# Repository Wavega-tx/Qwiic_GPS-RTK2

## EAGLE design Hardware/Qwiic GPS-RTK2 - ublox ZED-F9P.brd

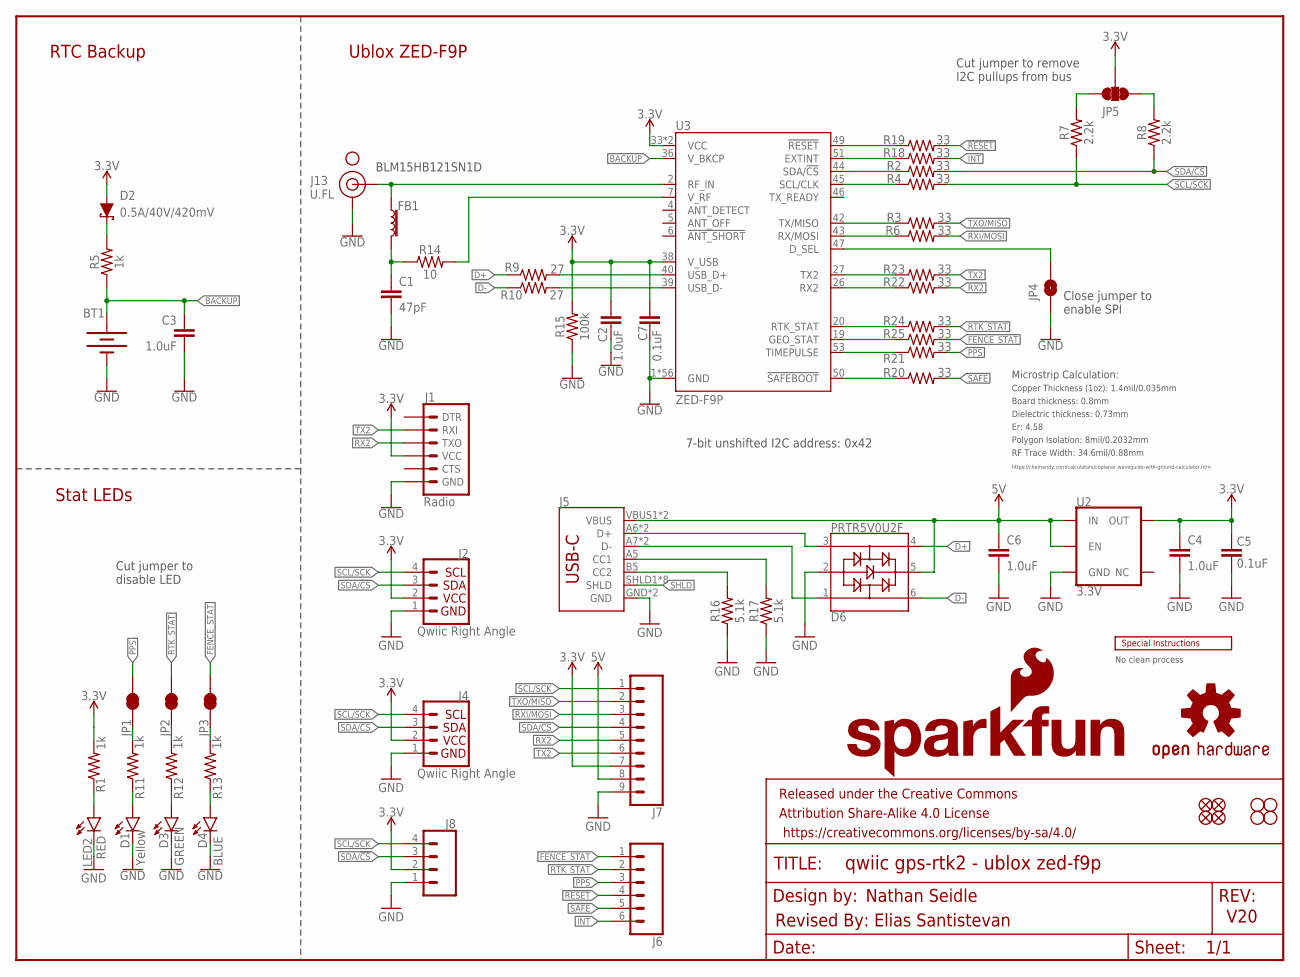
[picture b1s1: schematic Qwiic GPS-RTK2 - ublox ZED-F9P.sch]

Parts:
BT1: ML414H_IV01E_BATTERY; ML414H_IV01E
C1: 47pF; 0603
C2, C3, C4, C6: 1.0uF; 0603
C5, C7: 0.1uF; 0603
D1: Yellow; LED-0603
D2: 0.5A/40V/420mV; SOD-323
D3: GREEN; LED-0603
D4: BLUE; LED-0603
D6: PRTR5V0U2F; SOT886
FB1: FERRITE_BEAD-120_OHM-0402; 0402
FRAME1: FRAME-LETTER; CREATIVE_COMMONS
J1: Radio; 1X06_NO_SILK
J2, J4: Qwiic Right Angle; JST04_1MM_RA
J5: USB_C2-LAYER; USB-C-16P
J6: CONN_06NO_SILK_FEMALE_PTH; 1X06_NO_SILK
J7: CONN_09NO_SILK; 1X09_NO_SILK
J8: CONN_041X04_NO_SILK; 1X04_NO_SILK
J13: U.FL
JP1, JP2, JP3: JUMPER-SMT_2_NC_TRACE_SILK; SMT-JUMPER_2_NC_TRACE_SILK
JP4: JUMPER-SMT_2_NO_SILK; SMT-JUMPER_2_NO_SILK
JP5: JUMPER-SMT_3_2-NC_TRACE_SILK; SMT-JUMPER_3_2-NC_TRACE_SILK
JP21, JP61, JP71, JP81: FIDUCIALUFIDUCIAL; FIDUCIAL-MICRO
JP31, JP41, JP91, JP101: STAND-OFFTIGHT; STAND-OFF-TIGHT
LED2: RED; LED-0603
LOGO1: OSHW-LOGOMINI; OSHW-LOGO-MINI
LOGO2: SFE_LOGO_NAME_FLAME.1_INCH; SFE_LOGO_NAME_FLAME_.1
R1, R5, R11, R12, R13: 1k; 0603
R2, R3, R4, R6, R18, R19, R20, R21, R22, R23, R24, R25: 33; 0603
R7, R8: 2.2k; 0603
R9, R10: 27; 0603
R14: 10; 0603
R15: 100k; 0603
R16, R17: 5.1k; 0603
U2: 3.3V; SOT23-5
U3: ZED-F9P
U$2: SPECIAL_INSTRUCTIONS-ORDERING; ORDERING_INSTRUCTIONS
U$54: SMA-ANTENNA-THREADED; SMA-THREADED

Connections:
3.3V: C2.1, C4.1, C5.2, C7.2, D2.A, J1.4 (VCC), J2.2, J4.2, J7.7, J8.2, JP5.2, R1.2, R15.2, U2.5 (OUT), U3.33 (VCC), U3.34 (VCC), U3.38 (V_USB)
5V: C6.1, D6.5, J5.VBUS1 (VBUS), J5.VBUS2 (VBUS), J7.8, U2.1 (IN), U2.3 (EN)
!RESET: J6.4, R19.2
!SAFE: J6.5, R20.2
ANT_VCC: C1.1, FB1.2, R14.1
BACKUP: BT1.+, C3.1, R5.1, U3.36 (V_BKCP)
CC1: J5.A5 (CC1), R17.2
CC2: J5.B5 (CC2), R16.2
D+: D6.4, R9.1
D-: D6.6, R10.1
D_SEL: JP4.2, U3.47 (D_SEL)
FENCE_STAT: J6.1, JP3.2, R25.2
GND: BT1.-, C1.2, C2.2, C3.2, C4.2, C5.1, C6.2, C7.1, D1.C, D3.C, D4.C, D6.2, J1.6 (GND), J2.1, J4.1, J5.GND, J5.GND2 (GND), J7.9, J8.1, J13.1 (GND), J13.2 (GND), JP4.1, LED2.C, R15.1, R16.1, R17.1, U2.2 (GND), U3.1 (GND), U3.3 (GND), U3.12 (GND), U3.14 (GND), U3.32 (GND), U3.37 (GND), U3.41 (GND), U3.48 (GND), U3.55 (GND), U3.56 (GND), U3.57 (GND), U3.58 (GND), U3.59 (GND), U3.60 (GND), U3.61 (GND), U3.62 (GND), U3.63 (GND), U3.64 (GND), U3.65 (GND), U3.66 (GND), U3.67 (GND), U3.68 (GND), U3.69 (GND), U3.70 (GND), U3.71 (GND), U3.72 (GND), U3.73 (GND), U3.74 (GND), U3.75 (GND), U3.76 (GND), U3.77 (GND), U3.78 (GND), U3.79 (GND), U3.80 (GND), U3.81 (GND), U3.82 (GND), U3.83 (GND), U3.84 (GND), U3.85 (GND), U3.86 (GND), U3.87 (GND), U3.88 (GND), U3.89 (GND), U3.90 (GND), U3.91 (GND), U3.92 (GND), U3.93 (GND), U3.94 (GND), U3.95 (GND), U3.96 (GND), U3.97 (GND), U3.98 (GND), U3.99 (GND), U3.100 (GND), U3.101 (GND), U3.102 (GND)
GPS_ANT1: FB1.1, J13.FEED (SIGNAL), U3.2 (RF_IN)
INT: J6.6, R18.2
unnamed: D3.A, R12.1
unnamed: D1.A, R11.1
unnamed: JP2.1, R12.2
unnamed: JP1.1, R11.2
unnamed: JP5.1, R8.2
unnamed: D2.C, R5.2
unnamed: D4.A, R13.1
unnamed: JP5.3, R7.2
unnamed: JP3.1, R13.2
unnamed: LED2.A, R1.1
unnamed: R9.2, U3.40 (USB_D+)
unnamed: R10.2, U3.39 (USB_D-)
unnamed: R14.2, U3.7 (V_RF)
unnamed: R22.1, U3.26 (RX2)
unnamed: R18.1, U3.51 (EXTINT)
unnamed: R19.1, U3.49 (!RESET!)
unnamed: R21.1, U3.53 (TIMEPULSE)
unnamed: R20.1, U3.50 (!SAFEBOOT!)
unnamed: R24.1, U3.20 (RTK_STAT)
unnamed: R25.1, U3.19 (GEO_STAT)
PPS: J6.3, JP1.2, R21.2
RTK_STAT: J6.2, JP2.2, R24.2
RX2: J1.3 (TXO), J7.5, R22.2
RXI/MOSI: J7.3, R6.2
RXLV: R6.1, U3.43 (RX/MOSI)
SCL/SCK: J2.4, J4.4, J7.1, J8.4, R4.2, R7.1
SCL_LV: R4.1, U3.45 (SCL/CLK)
SDA/!CS: J2.3, J4.3, J7.4, J8.3, R2.2, R8.1
SDA_LV: R2.1, U3.44 (SDA/!CS!)
SHLD: J5.SHLD1 (SHLD), J5.SHLD2 (SHLD), J5.SHLD3 (SHLD), J5.SHLD4 (SHLD), J5.SHLD5 (SHLD), J5.SHLD6 (SHLD), J5.SHLD7 (SHLD), J5.SHLD8 (SHLD)
TX2: J1.2 (RXI), J7.6, R23.2
TX2_P: R23.1, U3.27 (TX2)
TXLV: R3.1, U3.42 (TX/MISO)
TXO/MISO: J7.2, R3.2
UNP_D+: D6.3, J5.A6 (D+), J5.B6 (D+)
UNP_D-: D6.1, J5.A7 (D-), J5.B7 (D-)

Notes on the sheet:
V20
7-bit unshifted I2C address: 0x42
Ublox ZED-F9P
RTC Backup
Stat LEDs
Cut jumper to remove I2C pullups from bus
Cut jumper to disable LED
Close jumper to enable SPI
BLM15HB121SN1D
Board thickness: 0.8mm
Er: 4.58
Copper Thickness (1oz): 1.4mil/0.035mm
RF Trace Width: 34.6mil/0.88mm
Polygon Isolation: 8mil/0.2032mm
No clean process
Dielectric thickness: 0.73mm
https://chemandy.com/calculators/coplanar-waveguide-with-ground-calculator.htm
Microstrip Calculation:
Nathan Seidle
Revised By: Elias Santistevan

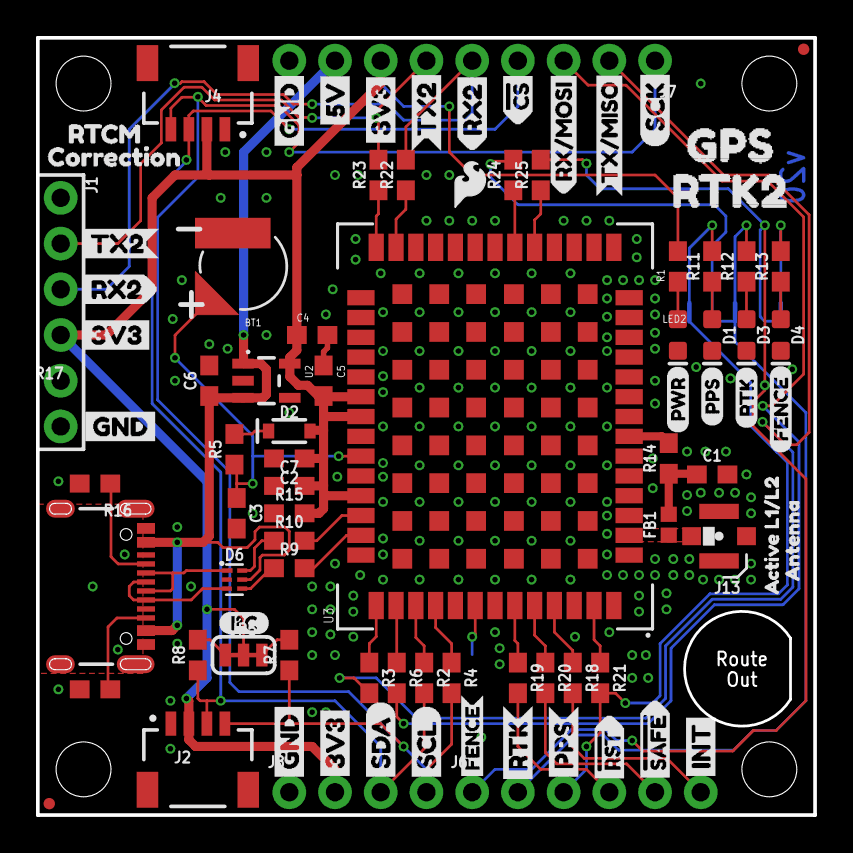
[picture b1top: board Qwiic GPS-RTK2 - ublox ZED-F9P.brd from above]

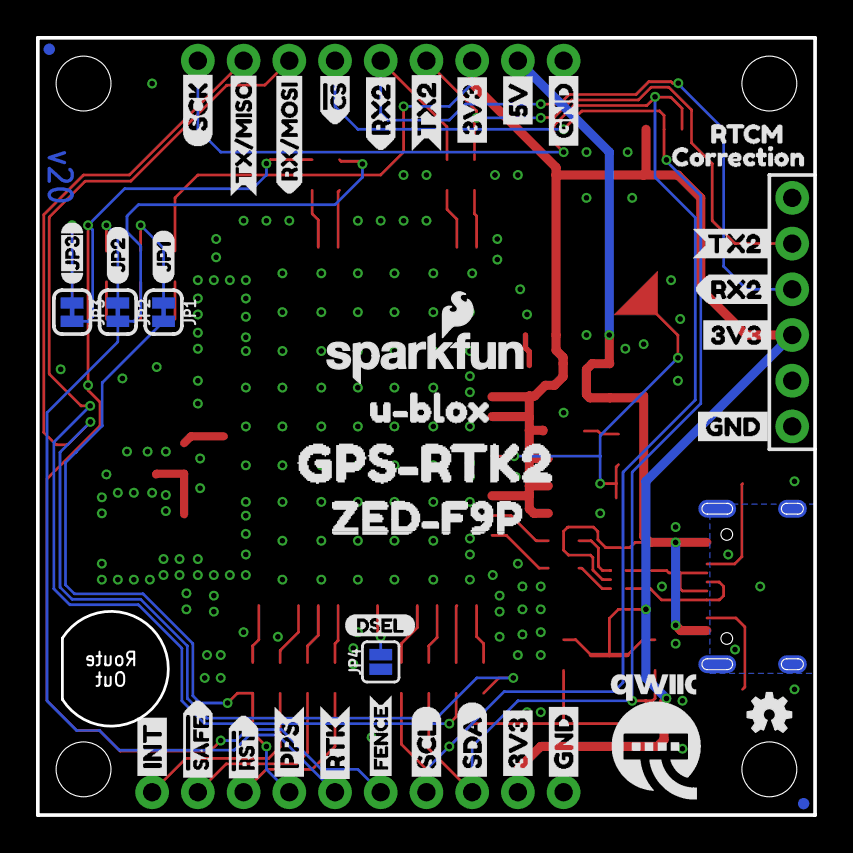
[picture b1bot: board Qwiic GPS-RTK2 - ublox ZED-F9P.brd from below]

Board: 2 copper layers, 43.2 x 43.2 mm, 136 parts (41 on the bottom side), 51 nets.

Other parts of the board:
U$1, U$4: SDA-[)
U$3, U$5: SCL-[)
U$6, U$7, U$60, U$61, U$66, U$67: 3V3-04
U$8, U$9, U$62, U$63: GND-04
U$10: I_SUPER2_C-()-03
U$11: FENCE2
U$12: JP20
U$13, U$28, U$29: RTK1
U$14, U$17: FENCE0
U$15, U$16: INT8
U$18: PWR-()-03
U$19, U$20: 5V
U$21, U$56, U$58: RX20
U$22: U#BLOX3
U$23, U$24: CS#-<]
U$25: JP10
U$26, U$31: RX#MOSI3
U$27: DSEL0
U$30: QWIIC-LOGO-MEDIUM
U$32: JP32
U$33: SFE_LOGO_FLAME_.1
U$34, U$37: TX#MISO1
U$35, U$36: #RST3
U$38, U$41: SCK-(]-04
U$39, U$40: #SAFE1
U$42: RX22
U$43, U$44: PPS5
U$45, U$68: GND3
U$46: GPS#RTK28
U$48, U$70: RTCM5
U$49: ZED#F9P6
U$50, U$55, U$57: TX21
U$51: TX23
U$52: PPS0
U$53, U$69: CORRECTION0
U$59: GPS0
U$64: RTK21
U$65: ACTIVE_L1#L21
U$71: ANTENNA2

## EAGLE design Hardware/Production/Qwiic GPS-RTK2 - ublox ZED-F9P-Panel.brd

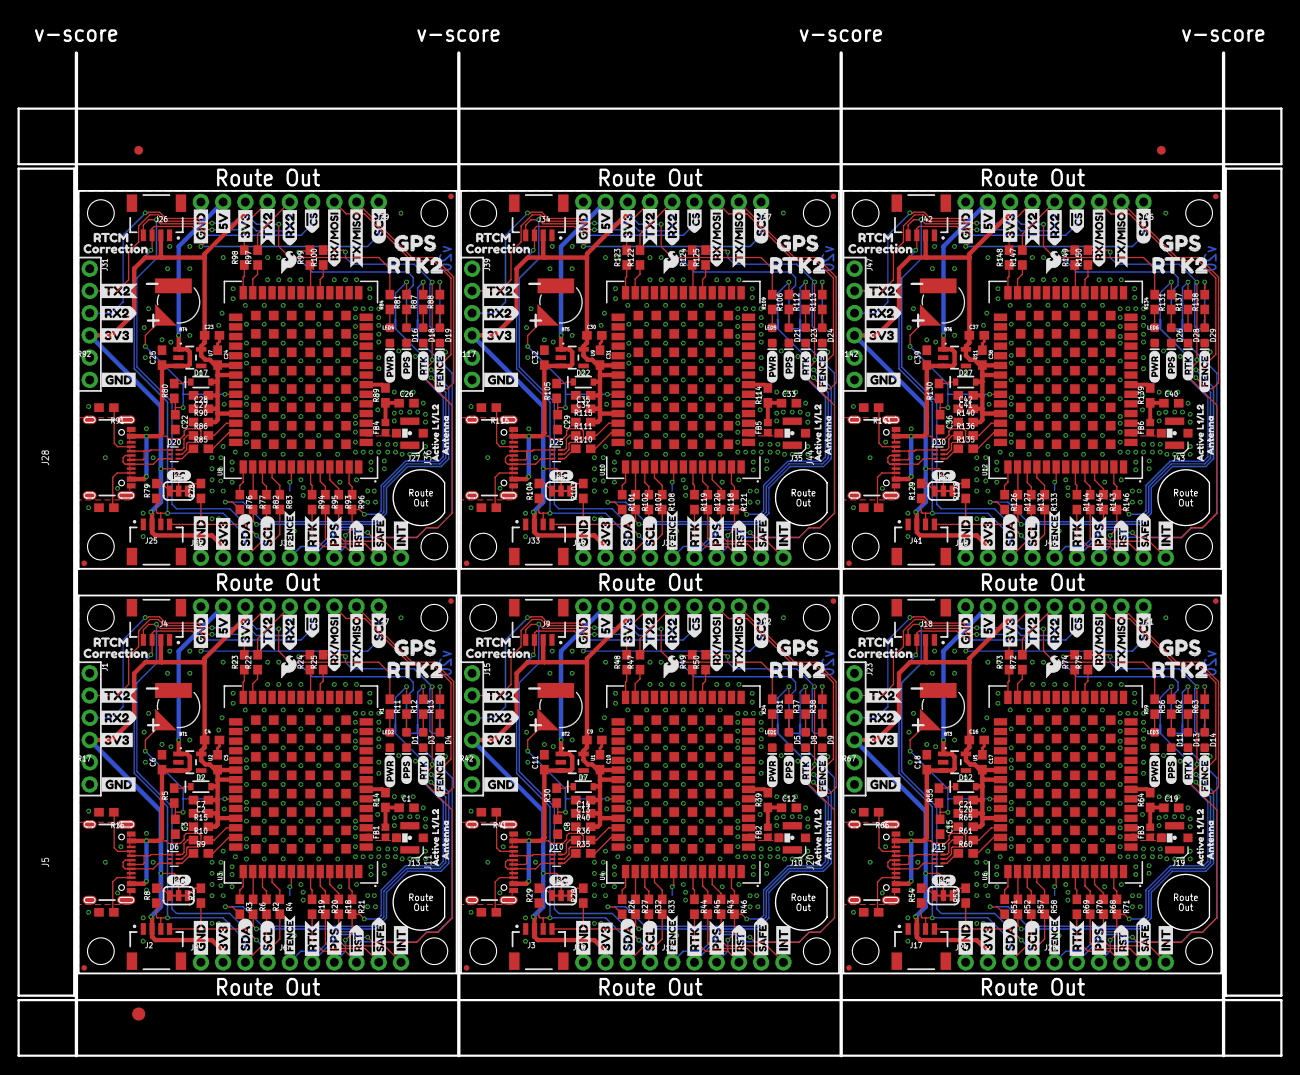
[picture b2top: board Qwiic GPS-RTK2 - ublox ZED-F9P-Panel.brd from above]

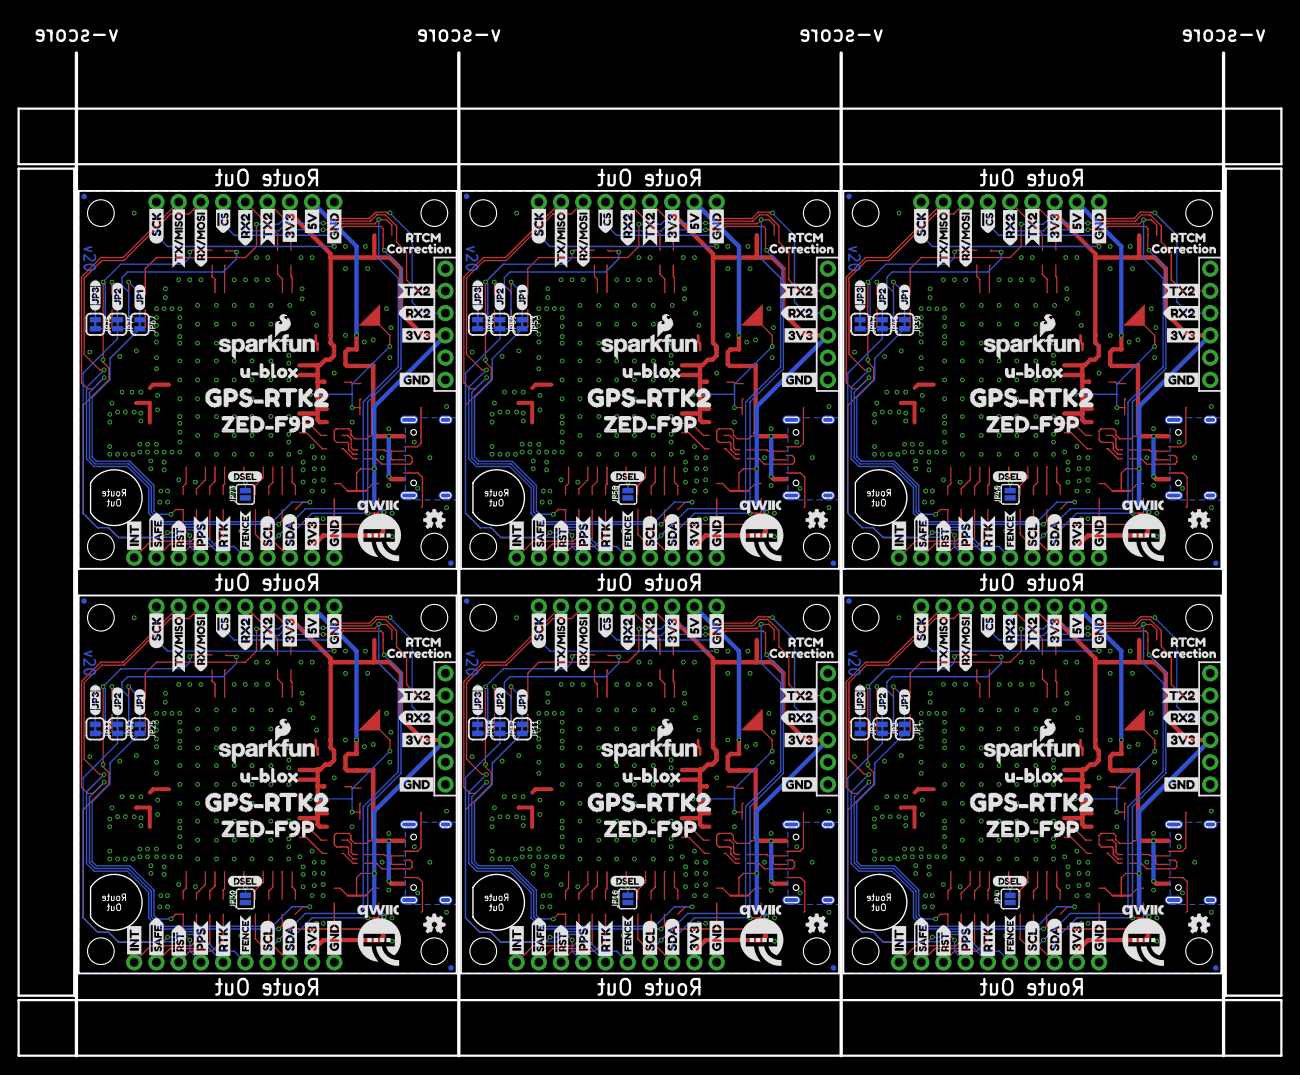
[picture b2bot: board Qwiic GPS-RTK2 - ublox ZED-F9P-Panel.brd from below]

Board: 2 copper layers, 144.3 x 114.6 mm, 807 parts (246 on the bottom side), 306 nets.

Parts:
BT1, BT2, BT3, BT4, BT5, BT6: ML414H_IV01E_BATTERY; ML414H_IV01E
C1, C12, C19, C26, C33, C40: 47pF; 0603
C2, C3, C4, C6, C8, C9, C11, C13, C15, C16, C18, C20, C22, C23, C25, C27, C29, C30, C32, C34, C36, C37, C39, C41: 1.0uF; 0603
C5, C7, C10, C14, C17, C21, C24, C28, C31, C35, C38, C42: 0.1uF; 0603
D1, D5, D11, D16, D21, D26: Yellow; LED-0603
D2, D7, D12, D17, D22, D27: 0.5A/40V/420mV; SOD-323
D3, D8, D13, D18, D23, D28: GREEN; LED-0603
D4, D9, D14, D19, D24, D29: BLUE; LED-0603
D6, D10, D15, D20, D25, D30: PRTR5V0U2F; SOT886
E$1, E$2: FIDUCIAL-1X2
E$3: FIDUCIAL-1.5X3
FB1, FB2, FB3, FB4, FB5, FB6: FERRITE_BEAD-120_OHM-0402; 0402
J1, J15, J23, J31, J39, J47: Radio; 1X06_NO_SILK
J2, J3, J4, J9, J17, J18, J25, J26, J33, J34, J41, J42: Qwiic Right Angle; JST04_1MM_RA
J5, J11, J20, J28, J36, J44: USB-C-16P
J6, J14, J22, J30, J38, J46: 1X06_NO_SILK
J7, J12, J21, J29, J37, J45: 1X09_NO_SILK
J8, J16, J24, J32, J40, J48: 1X04_NO_SILK
J10, J13, J19, J27, J35, J43: U.FL
JP1, JP2, JP3, JP11, JP17, JP18, JP25, JP32, JP33, JP39, JP46, JP47, JP53, JP59, JP60, JP67, JP74, JP75: JUMPER-SMT_2_NC_TRACE_SILK; SMT-JUMPER_2_NC_TRACE_SILK
JP4, JP16, JP30, JP45, JP58, JP73: JUMPER-SMT_2_NO_SILK; SMT-JUMPER_2_NO_SILK
JP5, JP10, JP24, JP38, JP52, JP66: JUMPER-SMT_3_2-NC_TRACE_SILK; SMT-JUMPER_3_2-NC_TRACE_SILK
JP6, JP7, JP14, JP15, JP19, JP20, JP28, JP29, JP31, JP34, JP35, JP41, JP43, JP44, JP48, JP49, JP56, JP57, JP62, JP63, JP70, JP72, JP91, JP101: STAND-OFFTIGHT; STAND-OFF-TIGHT
JP8, JP9, JP12, JP13, JP21, JP22, JP23, JP26, JP27, JP36, JP37, JP40, JP42, JP50, JP51, JP54, JP55, JP61, JP64, JP65, JP68, JP69, JP71, JP81: FIDUCIALUFIDUCIAL; FIDUCIAL-MICRO
LED1, LED2, LED3, LED4, LED5, LED6: RED; LED-0603
LOGO1, LOGO3, LOGO5, LOGO7, LOGO9, LOGO11: OSHW-LOGOMINI; OSHW-LOGO-MINI
LOGO2, LOGO4, LOGO6, LOGO8, LOGO10, LOGO12: SFE_LOGO_NAME_FLAME.1_INCH; SFE_LOGO_NAME_FLAME_.1
R1, R5, R11, R12, R13, R30, R31, R34, R37, R38, R55, R56, R59, R62, R63, R80, R81, R84, R87, R88, R105, R106, R109, R112, R113, R130, R131, R134, R137, R138: 1k; 0603
R2, R3, R4, R6, R18, R19, R20, R21, R22, R23, R24, R25, R26, R27, R32, R33, R43, R44, R45, R46, R47, R48, R49, R50, R51, R52, R57, R58, R68, R69, R70, R71, R72, R73, R74, R75, R76, R77, R82, R83, R93, R94, R95, R96, R97, R98, R99, R100, R101, R102, R107, R108, R118, R119, R120, R121, R122, R123, R124, R125, R126, R127, R132, R133, R143, R144, R145, R146, R147, R148, R149, R150: 33; 0603
R7, R8, R28, R29, R53, R54, R78, R79, R103, R104, R128, R129: 2.2k; 0603
R9, R10, R35, R36, R60, R61, R85, R86, R110, R111, R135, R136: 27; 0603
R14, R39, R64, R89, R114, R139: 10; 0603
R15, R40, R65, R90, R115, R140: 100k; 0603
R16, R17, R41, R42, R66, R67, R91, R92, R116, R117, R141, R142: 5.1k; 0603
U1, U2, U5, U7, U9, U11: 3.3V; SOT23-5
U3, U4, U6, U8, U10, U12: ZED-F9P
U$1, U$2, U$4, U$72, U$139, U$141, U$208, U$210, U$277, U$279, U$346, U$348: SDA-[)
U$3, U$5, U$47, U$73, U$140, U$142, U$209, U$211, U$278, U$280, U$347, U$349: SCL-[)
U$6, U$7, U$60, U$61, U$66, U$67, U$74, U$75, U$97, U$98, U$116, U$117, U$143, U$144, U$166, U$167, U$185, U$186, U$212, U$213, U$235, U$236, U$254, U$255, U$281, U$282, U$304, U$305, U$323, U$324, U$350, U$351, U$373, U$374, U$392, U$393: 3V3-04
U$8, U$9, U$62, U$63, U$76, U$77, U$99, U$100, U$145, U$146, U$168, U$169, U$214, U$215, U$237, U$238, U$283, U$284, U$306, U$307, U$352, U$353, U$375, U$376: GND-04
U$10, U$78, U$147, U$216, U$285, U$354: I_SUPER2_C-()-03
U$11, U$90, U$159, U$228, U$297, U$366: FENCE2
U$12, U$91, U$160, U$229, U$298, U$367: JP20
U$13, U$28, U$29, U$92, U$95, U$96, U$161, U$164, U$165, U$230, U$233, U$234, U$299, U$302, U$303, U$368, U$371, U$372: RTK1
U$14, U$17, U$93, U$94, U$162, U$163, U$231, U$232, U$300, U$301, U$369, U$370: FENCE0
U$15, U$16, U$79, U$80, U$148, U$149, U$217, U$218, U$286, U$287, U$355, U$356: INT8
U$18, U$104, U$173, U$242, U$311, U$380: PWR-()-03
U$19, U$20, U$105, U$106, U$174, U$175, U$243, U$244, U$312, U$313, U$381, U$382: 5V
U$21, U$56, U$58, U$129, U$134, U$136, U$198, U$203, U$205, U$267, U$272, U$274, U$336, U$341, U$343, U$405, U$410, U$412: RX20
U$22, U$81, U$150, U$219, U$288, U$357: U#BLOX3
U$23, U$24, U$107, U$108, U$176, U$177, U$245, U$246, U$314, U$315, U$383, U$384: CS#-<]
U$25, U$101, U$170, U$239, U$308, U$377: JP10
U$26, U$31, U$112, U$124, U$181, U$193, U$250, U$262, U$319, U$331, U$388, U$400: RX#MOSI3
U$27, U$103, U$172, U$241, U$310, U$379: DSEL0
U$30, U$82, U$151, U$220, U$289, U$358: QWIIC-LOGO-MEDIUM
U$32, U$102, U$171, U$240, U$309, U$378: JP32
U$33, U$111, U$180, U$249, U$318, U$387: SFE_LOGO_FLAME_.1
U$34, U$37, U$113, U$125, U$182, U$194, U$251, U$263, U$320, U$332, U$389, U$401: TX#MISO1
U$35, U$36, U$83, U$84, U$152, U$153, U$221, U$222, U$290, U$291, U$359, U$360: #RST3
U$38, U$41, U$109, U$110, U$178, U$179, U$247, U$248, U$316, U$317, U$385, U$386: SCK-(]-04
U$39, U$40, U$85, U$86, U$154, U$155, U$223, U$224, U$292, U$293, U$361, U$362: #SAFE1
U$42, U$130, U$199, U$268, U$337, U$406: RX22
U$43, U$44, U$87, U$88, U$156, U$157, U$225, U$226, U$294, U$295, U$363, U$364: PPS5
U$45, U$68, U$114, U$118, U$183, U$187, U$252, U$256, U$321, U$325, U$390, U$394: GND3
U$46, U$115, U$184, U$253, U$322, U$391: GPS#RTK28
U$48, U$70, U$120, U$122, U$189, U$191, U$258, U$260, U$327, U$329, U$396, U$398: RTCM5
U$49, U$121, U$190, U$259, U$328, U$397: ZED#F9P6
U$50, U$55, U$57, U$131, U$133, U$135, U$200, U$202, U$204, U$269, U$271, U$273, U$338, U$340, U$342, U$407, U$409, U$411: TX21
U$51, U$132, U$201, U$270, U$339, U$408: TX23
U$52, U$89, U$158, U$227, U$296, U$365: PPS0
U$53, U$69, U$119, U$123, U$188, U$192, U$257, U$261, U$326, U$330, U$395, U$399: CORRECTION0
U$54, U$126, U$195, U$264, U$333, U$402: SMA-ANTENNA-THREADED; SMA-THREADED
U$59, U$137, U$206, U$275, U$344, U$413: GPS0
U$64, U$138, U$207, U$276, U$345, U$414: RTK21
U$65, U$127, U$196, U$265, U$334, U$403: ACTIVE_L1#L21
U$71, U$128, U$197, U$266, U$335, U$404: ANTENNA2

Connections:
3.3V: C2.1, C4.1, C5.2, C7.2, D2.A, J1.4, J2.2, J4.2, J7.7, J8.2, JP5.2, R1.2, R15.2, U2.5, U3.33, U3.34, U3.38
3.3V1: C9.1, C10.2, C13.1, C14.2, D7.A, J3.2, J9.2, J12.7, J15.4, J16.2, JP10.2, R34.2, R40.2, U1.5, U4.33, U4.34, U4.38
3.3V2: C16.1, C17.2, C20.1, C21.2, D12.A, J17.2, J18.2, J21.7, J23.4, J24.2, JP24.2, R59.2, R65.2, U5.5, U6.33, U6.34, U6.38
3.3V3: C23.1, C24.2, C27.1, C28.2, D17.A, J25.2, J26.2, J29.7, J31.4, J32.2, JP38.2, R84.2, R90.2, U7.5, U8.33, U8.34, U8.38
3.3V4: C30.1, C31.2, C34.1, C35.2, D22.A, J33.2, J34.2, J37.7, J39.4, J40.2, JP52.2, R109.2, R115.2, U9.5, U10.33, U10.34, U10.38
3.3V5: C37.1, C38.2, C41.1, C42.2, D27.A, J41.2, J42.2, J45.7, J47.4, J48.2, JP66.2, R134.2, R140.2, U11.5, U12.33, U12.34, U12.38
5V: C6.1, D6.5, J5.VBUS1, J5.VBUS2, J7.8, U2.1, U2.3
5V1: C11.1, D10.5, J11.VBUS1, J11.VBUS2, J12.8, U1.1, U1.3
5V2: C18.1, D15.5, J20.VBUS1, J20.VBUS2, J21.8, U5.1, U5.3
5V3: C25.1, D20.5, J28.VBUS1, J28.VBUS2, J29.8, U7.1, U7.3
5V4: C32.1, D25.5, J36.VBUS1, J36.VBUS2, J37.8, U9.1, U9.3
5V5: C39.1, D30.5, J44.VBUS1, J44.VBUS2, J45.8, U11.1, U11.3
!RESET: J6.4, R19.2
!RESET1: J14.4, R44.2
!RESET2: J22.4, R69.2
!RESET3: J30.4, R94.2
!RESET4: J38.4, R119.2
!RESET5: J46.4, R144.2
!SAFE: J6.5, R20.2
!SAFE1: J14.5, R45.2
!SAFE2: J22.5, R70.2
!SAFE3: J30.5, R95.2
!SAFE4: J38.5, R120.2
!SAFE5: J46.5, R145.2
ANT_VCC: C1.1, FB1.2, R14.1
ANT_VCC1: C12.1, FB2.2, R39.1
ANT_VCC2: C19.1, FB3.2, R64.1
ANT_VCC3: C26.1, FB4.2, R89.1
ANT_VCC4: C33.1, FB5.2, R114.1
ANT_VCC5: C40.1, FB6.2, R139.1
BACKUP: BT1.+, C3.1, R5.1, U3.36
BACKUP1: BT2.+, C8.1, R30.1, U4.36
BACKUP2: BT3.+, C15.1, R55.1, U6.36
BACKUP3: BT4.+, C22.1, R80.1, U8.36
BACKUP4: BT5.+, C29.1, R105.1, U10.36
BACKUP5: BT6.+, C36.1, R130.1, U12.36
CC1: J5.A5, R17.2
CC2: J5.B5, R16.2
CC3: J11.A5, R42.2
CC4: J11.B5, R41.2
CC5: J20.A5, R67.2
CC6: J20.B5, R66.2
CC7: J28.A5, R92.2
CC8: J28.B5, R91.2
CC9: J36.A5, R117.2
CC10: J36.B5, R116.2
CC11: J44.A5, R142.2
CC12: J44.B5, R141.2
D+: D6.4, R9.1
D+1: D10.4, R35.1
D+2: D15.4, R60.1
D+3: D20.4, R85.1
D+4: D25.4, R110.1
D+5: D30.4, R135.1
D-: D6.6, R10.1
D-1: D10.6, R36.1
D-2: D15.6, R61.1
D-3: D20.6, R86.1
D-4: D25.6, R111.1
D-5: D30.6, R136.1
D_SEL: JP4.2, U3.47
D_SEL1: JP16.2, U4.47
D_SEL2: JP30.2, U6.47
D_SEL3: JP45.2, U8.47
D_SEL4: JP58.2, U10.47
D_SEL5: JP73.2, U12.47
FENCE_STAT: J6.1, JP3.2, R25.2
FENCE_STAT1: J14.1, JP18.2, R50.2
FENCE_STAT2: J22.1, JP33.2, R75.2
FENCE_STAT3: J30.1, JP47.2, R100.2
FENCE_STAT4: J38.1, JP60.2, R125.2
FENCE_STAT5: J46.1, JP75.2, R150.2
GND: BT1.-, C1.2, C2.2, C3.2, C4.2, C5.1, C6.2, C7.1, D1.C, D3.C, D4.C, D6.2, J1.6, J2.1, J4.1, J5.GND, J5.GND2, J7.9, J8.1, J13.1, J13.2, JP4.1, LED2.C, R15.1, R16.1, R17.1, U2.2, U3.1, U3.3, U3.12, U3.14, U3.32, U3.37, U3.41, U3.48, U3.55, U3.56, U3.57, U3.58, U3.59, U3.60, U3.61, U3.62, U3.63, U3.64, U3.65, U3.66, U3.67, U3.68, U3.69, U3.70, U3.71, U3.72, U3.73, U3.74, U3.75, U3.76, U3.77, U3.78, U3.79, U3.80, U3.81, U3.82, U3.83, U3.84, U3.85, U3.86, U3.87, U3.88, U3.89, U3.90, U3.91, U3.92, U3.93, U3.94, U3.95, U3.96, U3.97, U3.98, U3.99, U3.100, U3.101, U3.102
GND1: BT2.-, C8.2, C9.2, C10.1, C11.2, C12.2, C13.2, C14.1, D5.C, D8.C, D9.C, D10.2, J3.1, J9.1, J10.1, J10.2, J11.GND, J11.GND2, J12.9, J15.6, J16.1, JP16.1, LED1.C, R40.1, R41.1, R42.1, U1.2, U4.1, U4.3, U4.12, U4.14, U4.32, U4.37, U4.41, U4.48, U4.55, U4.56, U4.57, U4.58, U4.59, U4.60, U4.61, U4.62, U4.63, U4.64, U4.65, U4.66, U4.67, U4.68, U4.69, U4.70, U4.71, U4.72, U4.73, U4.74, U4.75, U4.76, U4.77, U4.78, U4.79, U4.80, U4.81, U4.82, U4.83, U4.84, U4.85, U4.86, U4.87, U4.88, U4.89, U4.90, U4.91, U4.92, U4.93, U4.94, U4.95, U4.96, U4.97, U4.98, U4.99, U4.100, U4.101, U4.102
GND2: BT3.-, C15.2, C16.2, C17.1, C18.2, C19.2, C20.2, C21.1, D11.C, D13.C, D14.C, D15.2, J17.1, J18.1, J19.1, J19.2, J20.GND, J20.GND2, J21.9, J23.6, J24.1, JP30.1, LED3.C, R65.1, R66.1, R67.1, U5.2, U6.1, U6.3, U6.12, U6.14, U6.32, U6.37, U6.41, U6.48, U6.55, U6.56, U6.57, U6.58, U6.59, U6.60, U6.61, U6.62, U6.63, U6.64, U6.65, U6.66, U6.67, U6.68, U6.69, U6.70, U6.71, U6.72, U6.73, U6.74, U6.75, U6.76, U6.77, U6.78, U6.79, U6.80, U6.81, U6.82, U6.83, U6.84, U6.85, U6.86, U6.87, U6.88, U6.89, U6.90, U6.91, U6.92, U6.93, U6.94, U6.95, U6.96, U6.97, U6.98, U6.99, U6.100, U6.101, U6.102
GND3: BT4.-, C22.2, C23.2, C24.1, C25.2, C26.2, C27.2, C28.1, D16.C, D18.C, D19.C, D20.2, J25.1, J26.1, J27.1, J27.2, J28.GND, J28.GND2, J29.9, J31.6, J32.1, JP45.1, LED4.C, R90.1, R91.1, R92.1, U7.2, U8.1, U8.3, U8.12, U8.14, U8.32, U8.37, U8.41, U8.48, U8.55, U8.56, U8.57, U8.58, U8.59, U8.60, U8.61, U8.62, U8.63, U8.64, U8.65, U8.66, U8.67, U8.68, U8.69, U8.70, U8.71, U8.72, U8.73, U8.74, U8.75, U8.76, U8.77, U8.78, U8.79, U8.80, U8.81, U8.82, U8.83, U8.84, U8.85, U8.86, U8.87, U8.88, U8.89, U8.90, U8.91, U8.92, U8.93, U8.94, U8.95, U8.96, U8.97, U8.98, U8.99, U8.100, U8.101, U8.102
GND4: BT5.-, C29.2, C30.2, C31.1, C32.2, C33.2, C34.2, C35.1, D21.C, D23.C, D24.C, D25.2, J33.1, J34.1, J35.1, J35.2, J36.GND, J36.GND2, J37.9, J39.6, J40.1, JP58.1, LED5.C, R115.1, R116.1, R117.1, U9.2, U10.1, U10.3, U10.12, U10.14, U10.32, U10.37, U10.41, U10.48, U10.55, U10.56, U10.57, U10.58, U10.59, U10.60, U10.61, U10.62, U10.63, U10.64, U10.65, U10.66, U10.67, U10.68, U10.69, U10.70, U10.71, U10.72, U10.73, U10.74, U10.75, U10.76, U10.77, U10.78, U10.79, U10.80, U10.81, U10.82, U10.83, U10.84, U10.85, U10.86, U10.87, U10.88, U10.89, U10.90, U10.91, U10.92, U10.93, U10.94, U10.95, U10.96, U10.97, U10.98, U10.99, U10.100, U10.101, U10.102
GND5: BT6.-, C36.2, C37.2, C38.1, C39.2, C40.2, C41.2, C42.1, D26.C, D28.C, D29.C, D30.2, J41.1, J42.1, J43.1, J43.2, J44.GND, J44.GND2, J45.9, J47.6, J48.1, JP73.1, LED6.C, R140.1, R141.1, R142.1, U11.2, U12.1, U12.3, U12.12, U12.14, U12.32, U12.37, U12.41, U12.48, U12.55, U12.56, U12.57, U12.58, U12.59, U12.60, U12.61, U12.62, U12.63, U12.64, U12.65, U12.66, U12.67, U12.68, U12.69, U12.70, U12.71, U12.72, U12.73, U12.74, U12.75, U12.76, U12.77, U12.78, U12.79, U12.80, U12.81, U12.82, U12.83, U12.84, U12.85, U12.86, U12.87, U12.88, U12.89, U12.90, U12.91, U12.92, U12.93, U12.94, U12.95, U12.96, U12.97, U12.98, U12.99, U12.100, U12.101, U12.102
GPS_ANT1: FB1.1, J13.FEED, U3.2
GPS_ANT2: FB2.1, J10.FEED, U4.2
GPS_ANT3: FB3.1, J19.FEED, U6.2
GPS_ANT4: FB4.1, J27.FEED, U8.2
GPS_ANT5: FB5.1, J35.FEED, U10.2
GPS_ANT6: FB6.1, J43.FEED, U12.2
INT: J6.6, R18.2
INT1: J14.6, R43.2
INT2: J22.6, R68.2
INT3: J30.6, R93.2
INT4: J38.6, R118.2
INT5: J46.6, R143.2
unnamed: D3.A, R12.1
unnamed: D1.A, R11.1
unnamed: JP2.1, R12.2
unnamed: JP1.1, R11.2
unnamed: JP5.1, R8.2
unnamed: D2.C, R5.2
unnamed: D4.A, R13.1
unnamed: JP5.3, R7.2
unnamed: JP3.1, R13.2
unnamed: LED2.A, R1.1
unnamed: R9.2, U3.40
unnamed: R10.2, U3.39
unnamed: R14.2, U3.7
unnamed: R22.1, U3.26
unnamed: R18.1, U3.51
unnamed: R19.1, U3.49
unnamed: R21.1, U3.53
unnamed: R20.1, U3.50
unnamed: R24.1, U3.20
unnamed: R25.1, U3.19
unnamed: JP10.1, R29.2
unnamed: JP10.3, R28.2
unnamed: D5.A, R31.1
unnamed: JP11.1, R31.2
unnamed: D7.C, R30.2
unnamed: LED1.A, R34.1
unnamed: R35.2, U4.40
unnamed: R36.2, U4.39
unnamed: D8.A, R37.1
unnamed: JP17.1, R37.2
unnamed: D9.A, R38.1
unnamed: JP18.1, R38.2
unnamed: R39.2, U4.7
unnamed: R47.1, U4.26
unnamed: R43.1, U4.51
unnamed: R44.1, U4.49
unnamed: R46.1, U4.53
unnamed: R45.1, U4.50
unnamed: R49.1, U4.20
unnamed: R50.1, U4.19
unnamed: JP24.1, R54.2
unnamed: JP24.3, R53.2
unnamed: D11.A, R56.1
unnamed: JP25.1, R56.2
unnamed: D12.C, R55.2
unnamed: LED3.A, R59.1
unnamed: R60.2, U6.40
unnamed: R61.2, U6.39
unnamed: D13.A, R62.1
unnamed: JP32.1, R62.2
unnamed: D14.A, R63.1
unnamed: JP33.1, R63.2
unnamed: R64.2, U6.7
unnamed: R72.1, U6.26
unnamed: R68.1, U6.51
unnamed: R69.1, U6.49
unnamed: R71.1, U6.53
unnamed: R70.1, U6.50
unnamed: R74.1, U6.20
unnamed: R75.1, U6.19
unnamed: JP38.1, R79.2
unnamed: JP38.3, R78.2
unnamed: D16.A, R81.1
unnamed: JP39.1, R81.2
unnamed: D17.C, R80.2
unnamed: LED4.A, R84.1
unnamed: R85.2, U8.40
unnamed: R86.2, U8.39
unnamed: D18.A, R87.1
unnamed: JP46.1, R87.2
unnamed: D19.A, R88.1
unnamed: JP47.1, R88.2
unnamed: R89.2, U8.7
unnamed: R97.1, U8.26
unnamed: R93.1, U8.51
unnamed: R94.1, U8.49
unnamed: R96.1, U8.53
unnamed: R95.1, U8.50
unnamed: R99.1, U8.20
unnamed: R100.1, U8.19
unnamed: JP52.1, R104.2
unnamed: JP52.3, R103.2
unnamed: D21.A, R106.1
unnamed: JP53.1, R106.2
unnamed: D22.C, R105.2
unnamed: LED5.A, R109.1
unnamed: R110.2, U10.40
unnamed: R111.2, U10.39
unnamed: D23.A, R112.1
unnamed: JP59.1, R112.2
unnamed: D24.A, R113.1
unnamed: JP60.1, R113.2
unnamed: R114.2, U10.7
unnamed: R122.1, U10.26
unnamed: R118.1, U10.51
unnamed: R119.1, U10.49
unnamed: R121.1, U10.53
unnamed: R120.1, U10.50
unnamed: R124.1, U10.20
unnamed: R125.1, U10.19
unnamed: JP66.1, R129.2
unnamed: JP66.3, R128.2
unnamed: D26.A, R131.1
unnamed: JP67.1, R131.2
unnamed: D27.C, R130.2
unnamed: LED6.A, R134.1
unnamed: R135.2, U12.40
unnamed: R136.2, U12.39
unnamed: D28.A, R137.1
unnamed: JP74.1, R137.2
unnamed: D29.A, R138.1
unnamed: JP75.1, R138.2
unnamed: R139.2, U12.7
unnamed: R147.1, U12.26
unnamed: R143.1, U12.51
unnamed: R144.1, U12.49
unnamed: R146.1, U12.53
unnamed: R145.1, U12.50
unnamed: R149.1, U12.20
unnamed: R150.1, U12.19
PPS: J6.3, JP1.2, R21.2
PPS1: J14.3, JP11.2, R46.2
PPS2: J22.3, JP25.2, R71.2
PPS3: J30.3, JP39.2, R96.2
PPS4: J38.3, JP53.2, R121.2
PPS5: J46.3, JP67.2, R146.2
RTK_STAT: J6.2, JP2.2, R24.2
RTK_STAT1: J14.2, JP17.2, R49.2
RTK_STAT2: J22.2, JP32.2, R74.2
RTK_STAT3: J30.2, JP46.2, R99.2
RTK_STAT4: J38.2, JP59.2, R124.2
RTK_STAT5: J46.2, JP74.2, R149.2
RX1: J12.5, J15.3, R47.2
RX2: J1.3, J7.5, R22.2
RX3: J21.5, J23.3, R72.2
RX4: J29.5, J31.3, R97.2
RX5: J37.5, J39.3, R122.2
RX6: J45.5, J47.3, R147.2
RXI/MOSI: J7.3, R6.2
RXI/MOSI1: J12.3, R27.2
RXI/MOSI2: J21.3, R52.2
RXI/MOSI3: J29.3, R77.2
RXI/MOSI4: J37.3, R102.2
RXI/MOSI5: J45.3, R127.2
RXLV: R6.1, U3.43
RXLV1: R27.1, U4.43
RXLV2: R52.1, U6.43
RXLV3: R77.1, U8.43
RXLV4: R102.1, U10.43
RXLV5: R127.1, U12.43
SCL/SCK: J2.4, J4.4, J7.1, J8.4, R4.2, R7.1
SCL/SCK1: J3.4, J9.4, J12.1, J16.4, R28.1, R33.2
SCL/SCK2: J17.4, J18.4, J21.1, J24.4, R53.1, R58.2
SCL/SCK3: J25.4, J26.4, J29.1, J32.4, R78.1, R83.2
SCL/SCK4: J33.4, J34.4, J37.1, J40.4, R103.1, R108.2
SCL/SCK5: J41.4, J42.4, J45.1, J48.4, R128.1, R133.2
SCL_LV: R4.1, U3.45
SCL_LV1: R33.1, U4.45
SCL_LV2: R58.1, U6.45
SCL_LV3: R83.1, U8.45
SCL_LV4: R108.1, U10.45
SCL_LV5: R133.1, U12.45
SDA/!CS: J2.3, J4.3, J7.4, J8.3, R2.2, R8.1
SDA/!CS1: J3.3, J9.3, J12.4, J16.3, R29.1, R32.2
SDA/!CS2: J17.3, J18.3, J21.4, J24.3, R54.1, R57.2
SDA/!CS3: J25.3, J26.3, J29.4, J32.3, R79.1, R82.2
SDA/!CS4: J33.3, J34.3, J37.4, J40.3, R104.1, R107.2
SDA/!CS5: J41.3, J42.3, J45.4, J48.3, R129.1, R132.2
SDA_LV: R2.1, U3.44
SDA_LV1: R32.1, U4.44
SDA_LV2: R57.1, U6.44
SDA_LV3: R82.1, U8.44
SDA_LV4: R107.1, U10.44
SDA_LV5: R132.1, U12.44
SHLD: J5.SHLD1, J5.SHLD2, J5.SHLD3, J5.SHLD4, J5.SHLD5, J5.SHLD6, J5.SHLD7, J5.SHLD8
SHLD1: J11.SHLD1, J11.SHLD2, J11.SHLD3, J11.SHLD4, J11.SHLD5, J11.SHLD6, J11.SHLD7, J11.SHLD8
SHLD2: J20.SHLD1, J20.SHLD2, J20.SHLD3, J20.SHLD4, J20.SHLD5, J20.SHLD6, J20.SHLD7, J20.SHLD8
SHLD3: J28.SHLD1, J28.SHLD2, J28.SHLD3, J28.SHLD4, J28.SHLD5, J28.SHLD6, J28.SHLD7, J28.SHLD8
SHLD4: J36.SHLD1, J36.SHLD2, J36.SHLD3, J36.SHLD4, J36.SHLD5, J36.SHLD6, J36.SHLD7, J36.SHLD8
SHLD5: J44.SHLD1, J44.SHLD2, J44.SHLD3, J44.SHLD4, J44.SHLD5, J44.SHLD6, J44.SHLD7, J44.SHLD8
TX1: J12.6, J15.2, R48.2
TX2: J1.2, J7.6, R23.2
TX2_P: R23.1, U3.27
TX2_P1: R48.1, U4.27
TX2_P2: R73.1, U6.27
TX2_P3: R98.1, U8.27
TX2_P4: R123.1, U10.27
TX2_P5: R148.1, U12.27
TX3: J21.6, J23.2, R73.2
TX4: J29.6, J31.2, R98.2
TX5: J37.6, J39.2, R123.2
TX6: J45.6, J47.2, R148.2
TXLV: R3.1, U3.42
TXLV1: R26.1, U4.42
TXLV2: R51.1, U6.42
TXLV3: R76.1, U8.42
TXLV4: R101.1, U10.42
TXLV5: R126.1, U12.42
TXO/MISO: J7.2, R3.2
TXO/MISO1: J12.2, R26.2
TXO/MISO2: J21.2, R51.2
TXO/MISO3: J29.2, R76.2
TXO/MISO4: J37.2, R101.2
TXO/MISO5: J45.2, R126.2
UNP_D+: D6.3, J5.A6, J5.B6
UNP_D+1: D10.3, J11.A6, J11.B6
UNP_D+2: D15.3, J20.A6, J20.B6
UNP_D+3: D20.3, J28.A6, J28.B6
UNP_D+4: D25.3, J36.A6, J36.B6
UNP_D+5: D30.3, J44.A6, J44.B6
UNP_D-: D6.1, J5.A7, J5.B7
UNP_D-1: D10.1, J11.A7, J11.B7
UNP_D-2: D15.1, J20.A7, J20.B7
UNP_D-3: D20.1, J28.A7, J28.B7
UNP_D-4: D25.1, J36.A7, J36.B7
UNP_D-5: D30.1, J44.A7, J44.B7

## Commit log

2020-01-10 Adds reflowable battery and uses all parts from SparkFun Libraries
2020-01-10 Adds panel for v20

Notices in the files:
parts and their libraries:
SparkFun-Resistors: Licensing: Creative Commons ShareAlike 4.0 International - https://creativecommons.org/licenses/by-sa/4.0
SparkFun-Aesthetics: Released under the Creative Commons Attribution Share-Alike 4.0 License
SparkFun-Aesthetics: https://creativecommons.org/licenses/by-sa/4.0
